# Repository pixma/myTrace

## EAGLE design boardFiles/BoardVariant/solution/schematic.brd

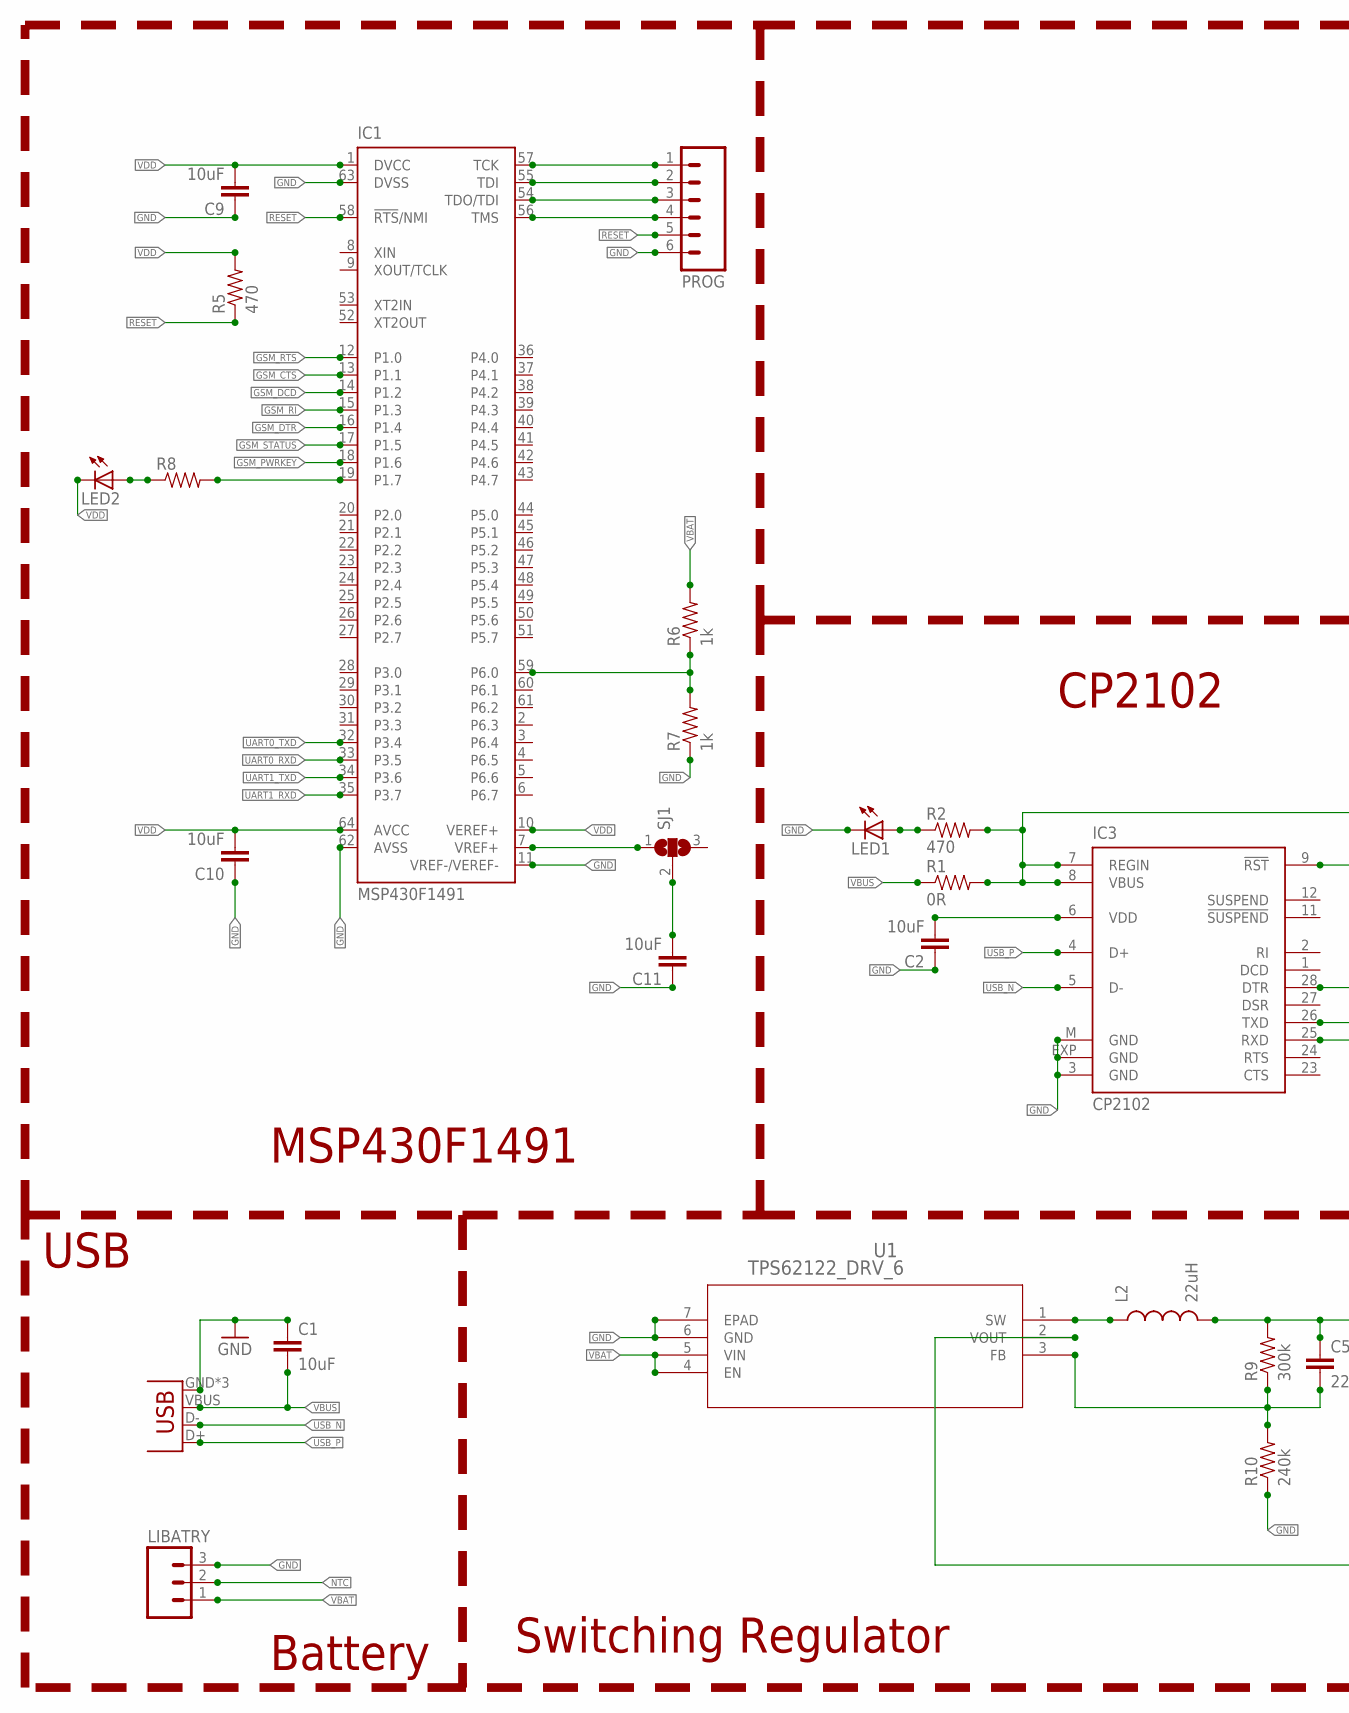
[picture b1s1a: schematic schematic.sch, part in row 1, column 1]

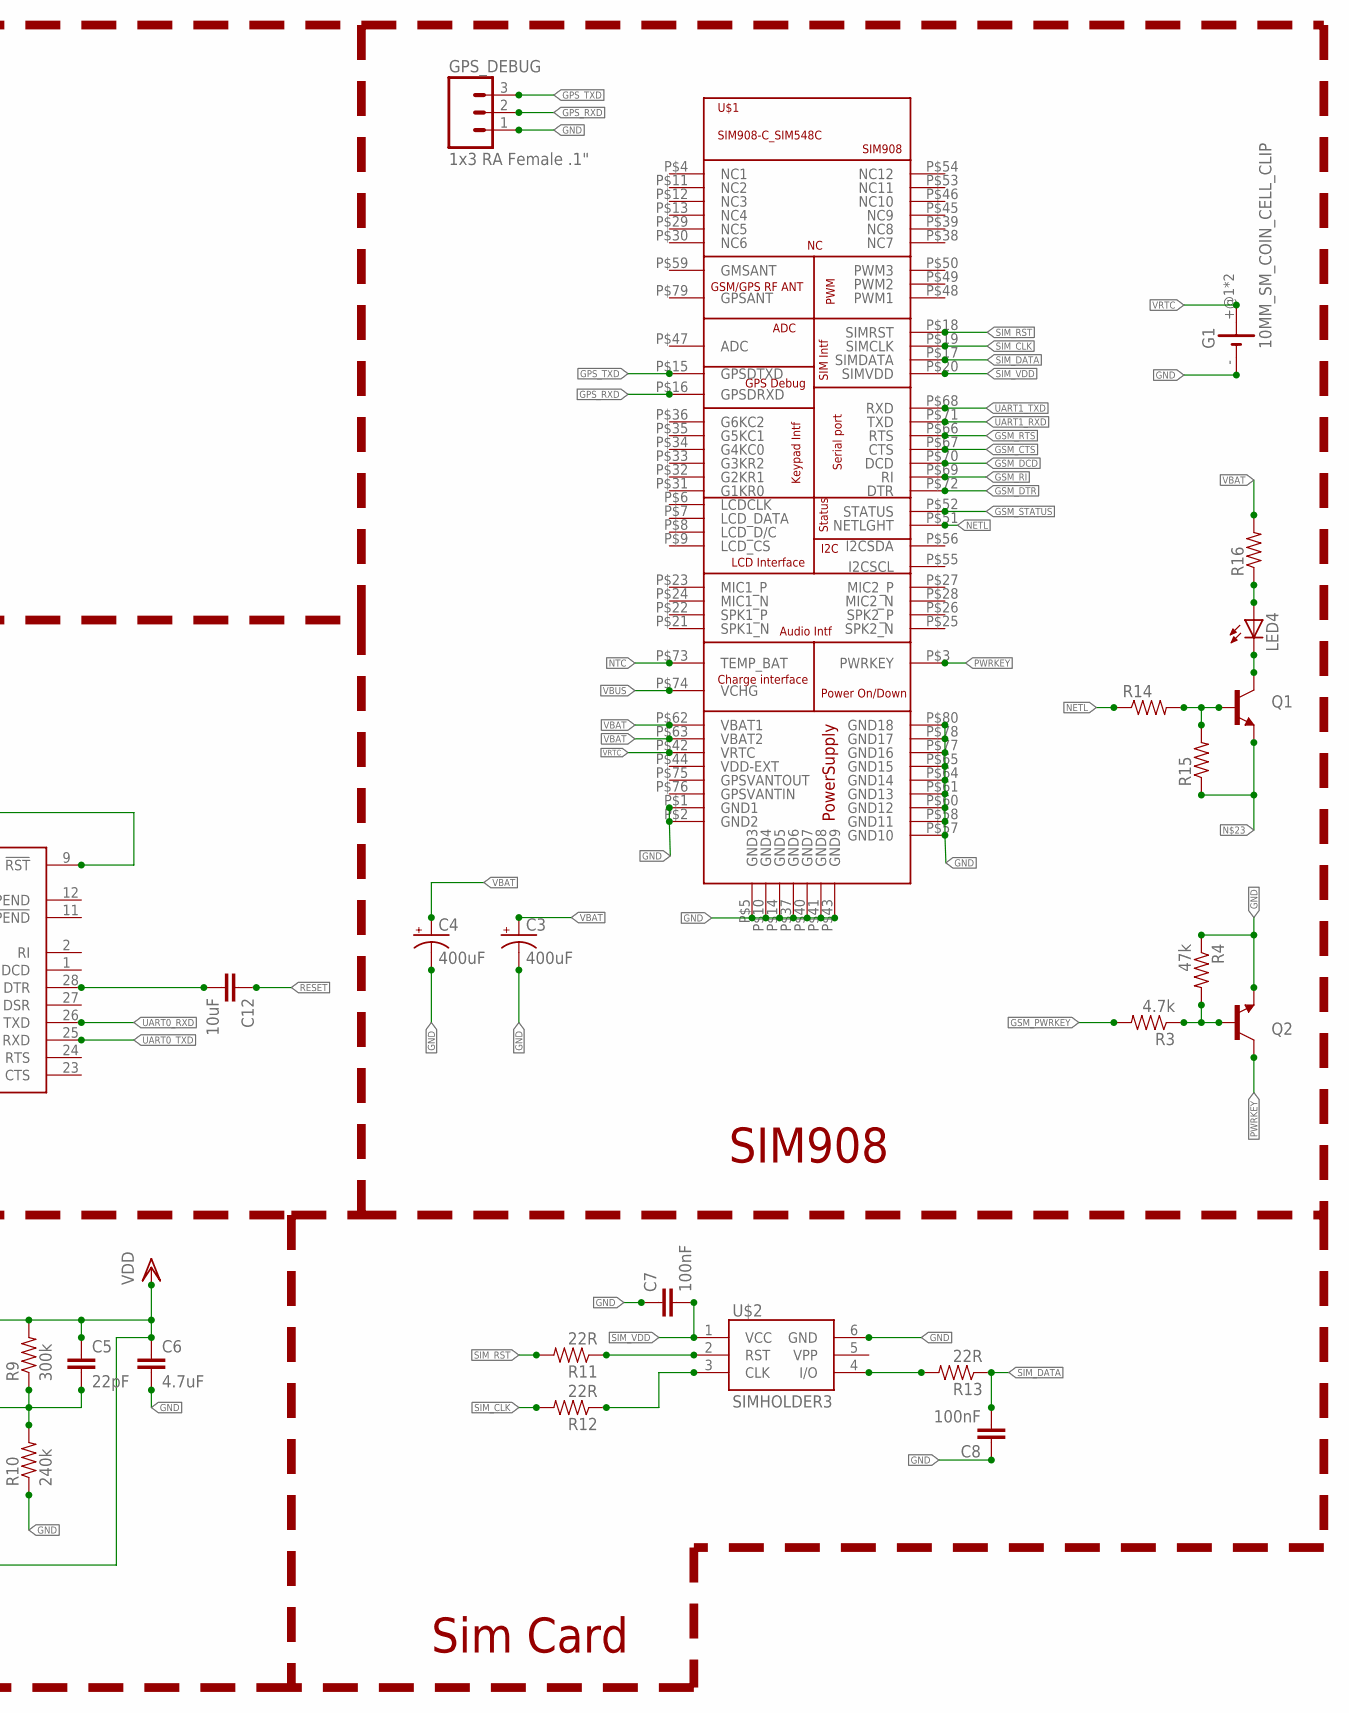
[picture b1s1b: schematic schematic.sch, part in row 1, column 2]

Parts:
C1, C2, C9, C10, C11, C12: 10uF; 0402-CAP
C3, C4: 400uF; PANASONIC_G
C5: 22pF; 0402-CAP
C6: 4.7uF; 0402-CAP
C7, C8: 100nF; 0402-CAP
G1: 10MM_SM_COIN_CELL_CLIP
GPS_DEBUG: 1x3 RA Female .1"; 1X03_SMD_RA_FEMALE
IC1: MSP430F1491; SQFP-S-10X10-64
IC3: CP2102; MLP28
JP1: USB-MICROB
L2: 22uH; C0402
LED1, LED2, LED4: LEDSML0603; SML0603
LIBATRY: M03PTH; 1X03
PROG: M06SMD-STRAIGHT; 1X06_SMD_STRAIGHT
Q1, Q2: TRANSISTOR_NPNSOT23; SOT23
R1: 0R; 0402-RES
R2, R5: 470; 0402-RES
R3: 4.7k; 0402-RES
R4: 47k; 0402-RES
R6, R7: 1k; 0402-RES
R8, R14, R15, R16: RESISTOR0402-RES; 0402-RES
R9: 300k; 0402-RES
R10: 240k; 0402-RES
R11, R12, R13: 22R; 0402-RES
SJ1: SJ2W; SJ_2
U1: TPS62122_DRV_6; DRV6_1P6X1
U$1: SIM908-C_SIM548C
U$2: SIMHOLDER3

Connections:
GND: C1.1, C2.1, C3.-, C4.-, C6.2, C7.1, C8.1, C9.1, C10.1, C11.1, G1.-, GPS_DEBUG.1, IC1.11 (VREF-/VEREF-), IC1.62 (AVSS), IC1.63 (DVSS), IC3.3 (GND), IC3.EXP (GND), IC3.M (GND), JP1.GND, JP1.MT1 (GND), JP1.MT2 (GND), LED1.C, LIBATRY.3, PROG.6, Q2.2 (E), R4.1, R7.1, R10.1, U1.6 (GND), U1.7 (EPAD), U$1.P$1 (GND1), U$1.P$2 (GND2), U$1.P$5 (GND3), U$1.P$10 (GND4), U$1.P$14 (GND5), U$1.P$37 (GND6), U$1.P$40 (GND7), U$1.P$41 (GND8), U$1.P$43 (GND9), U$1.P$57 (GND10), U$1.P$58 (GND11), U$1.P$60 (GND12), U$1.P$61 (GND13), U$1.P$64 (GND14), U$1.P$65 (GND15), U$1.P$77 (GND16), U$1.P$78 (GND17), U$1.P$80 (GND18), U$2.6 (GND)
GPS_RXD: GPS_DEBUG.2, U$1.P$16 (GPSDRXD)
GPS_TXD: GPS_DEBUG.3, U$1.P$15 (GPSDTXD)
GSM_CTS: IC1.13 (P1.1), U$1.P$67 (CTS)
GSM_DCD: IC1.14 (P1.2), U$1.P$70 (DCD)
GSM_DTR: IC1.16 (P1.4), U$1.P$72 (DTR)
GSM_PWRKEY: IC1.18 (P1.6), R3.2
GSM_RI: IC1.15 (P1.3), U$1.P$69 (RI)
GSM_RTS: IC1.12 (P1.0), U$1.P$66 (RTS)
GSM_STATUS: IC1.17 (P1.5), U$1.P$52 (STATUS)
unnamed: IC1.57 (TCK), PROG.1
unnamed: IC1.7 (VREF+), SJ1.1
unnamed: IC1.55 (TDI), PROG.2
unnamed: LED4.C, Q1.3 (C)
unnamed: LED1.A, R2.1
unnamed: IC1.54 (TDO/TDI), PROG.3
unnamed: LED4.A, R16.1
unnamed: Q2.1 (B), R3.1, R4.2
unnamed: IC1.56 (TMS), PROG.4
unnamed: R11.1, U$2.2 (RST)
unnamed: C2.2, IC3.6 (VDD)
unnamed: L2.1, U1.1 (SW)
unnamed: LED2.A, R8.1
unnamed: C11.2, SJ1.2
unnamed: IC3.7 (REGIN), IC3.8 (VBUS), IC3.9 (!RST), R1.2, R2.2
unnamed: R12.1, U$2.3 (CLK)
unnamed: R13.2, U$2.4 (I/O)
unnamed: C5.2, R9.1, R10.2, U1.3 (FB)
unnamed: IC1.59 (P6.0), R6.1, R7.2
unnamed: C12.2, IC3.28 (DTR)
unnamed: Q1.2 (E), R15.1
unnamed: Q1.1 (B), R14.2, R15.2
unnamed: IC1.19 (P1.7), R8.2
NETL: R14.1, U$1.P$51 (NETLGHT)
NTC: LIBATRY.2, U$1.P$73 (TEMP_BAT)
PWRKEY: Q2.3 (C), U$1.P$3 (PWRKEY)
RESET: C12.1, IC1.58 (!RTS!/NMI), PROG.5, R5.1
SIM_CLK: R12.2, U$1.P$19 (SIMCLK)
SIM_DATA: C8.2, R13.1, U$1.P$17 (SIMDATA)
SIM_RST: R11.2, U$1.P$18 (SIMRST)
SIM_VDD: C7.2, U$1.P$20 (SIMVDD), U$2.1 (VCC)
UART0_RXD: IC1.33 (P3.5), IC3.26 (TXD)
UART0_TXD: IC1.32 (P3.4), IC3.25 (RXD)
UART1_RXD: IC1.35 (P3.7), U$1.P$71 (TXD)
UART1_TXD: IC1.34 (P3.6), U$1.P$68 (RXD)
USB_N: IC3.5 (D-), JP1.D-
USB_P: IC3.4 (D+), JP1.D+
VBAT: C3.+, C4.+, LIBATRY.1, R6.2, R16.2, U1.4 (EN), U1.5 (VIN), U$1.P$62 (VBAT1), U$1.P$63 (VBAT2)
VBUS: C1.2, JP1.VBUS, R1.1, U$1.P$74 (VCHG)
VDD: C5.1, C6.1, C9.2, C10.2, IC1.1 (DVCC), IC1.10 (VEREF+), IC1.64 (AVCC), L2.2, LED2.C, R5.2, R9.2, U1.2 (VOUT)
VRTC: G1.+@1 (+), G1.+@2 (+), U$1.P$42 (VRTC)

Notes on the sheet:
MSP430F1491
USB
Switching Regulator
Sim Card
SIM908
CP2102
Battery

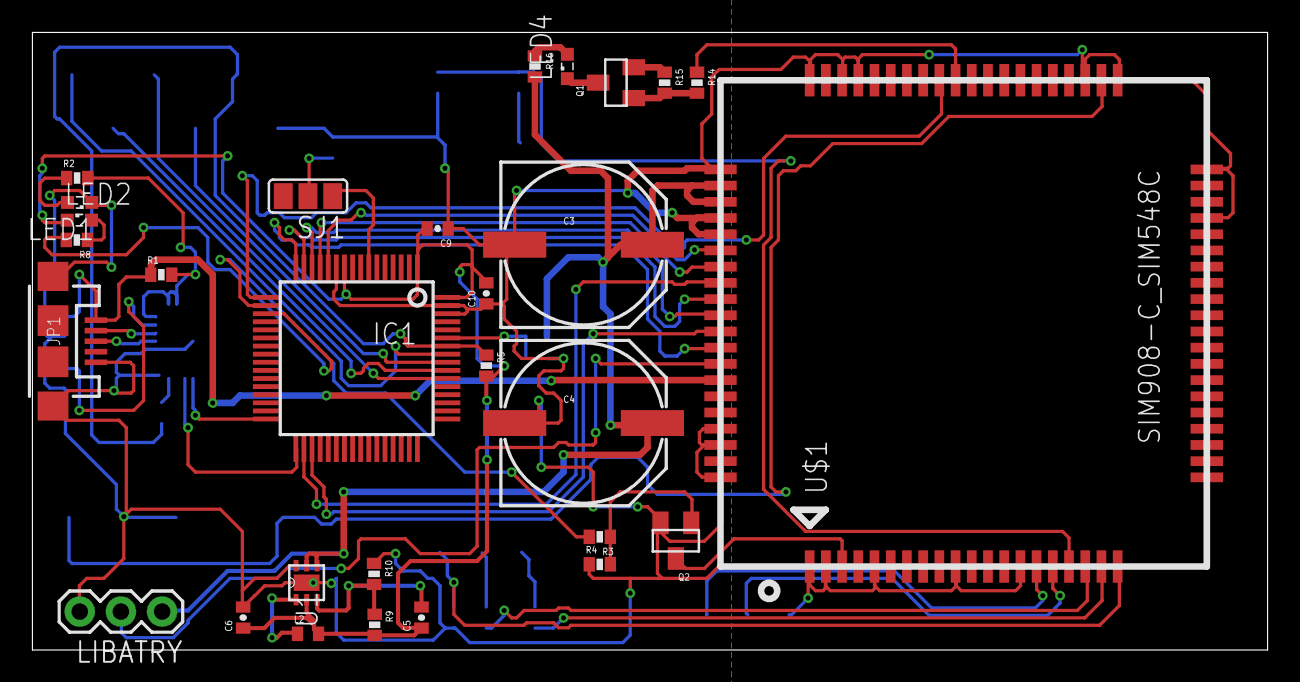
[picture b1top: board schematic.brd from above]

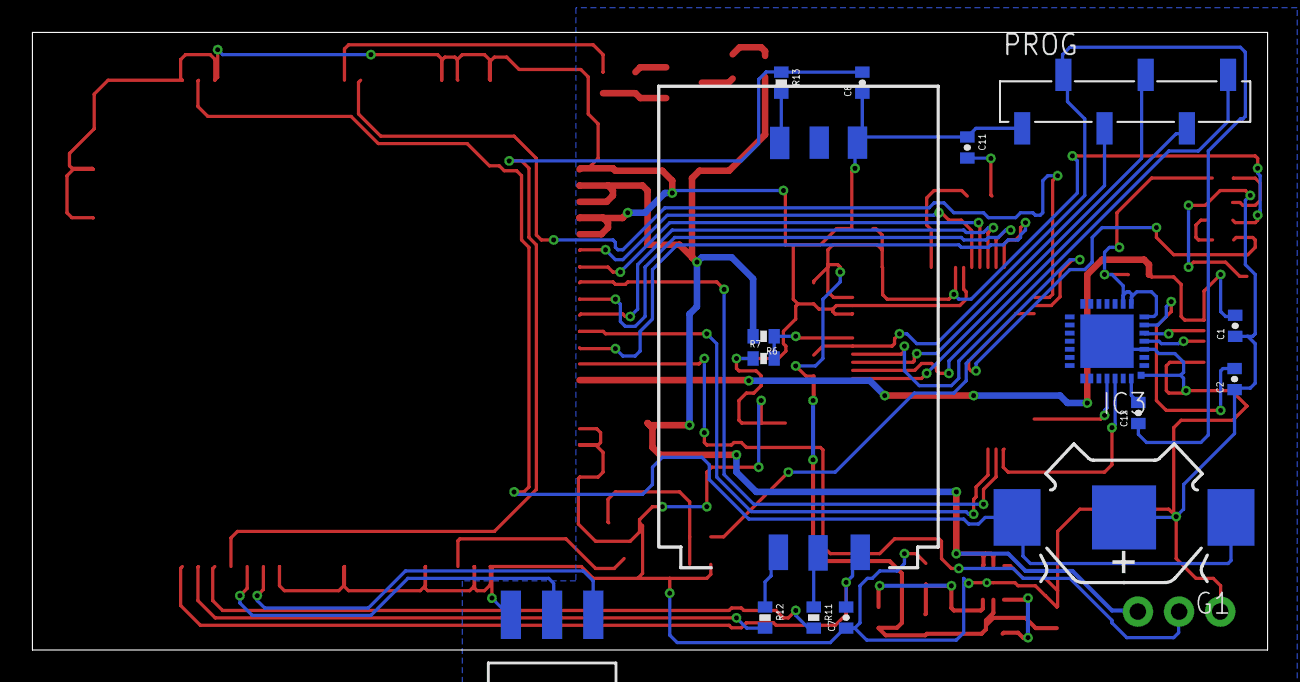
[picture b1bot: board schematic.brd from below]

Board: 2 copper layers, 76.2 x 38.1 mm, 45 parts (16 on the bottom side), 51 nets.

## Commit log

2014-09-12 Normal Push.
2014-09-15 Normal Push

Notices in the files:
parts and their libraries:
SparkFun-Connectors: Licensing: Creative Commons ShareAlike 4.0 International - https://creativecommons.org/licenses/by-sa/4.0
